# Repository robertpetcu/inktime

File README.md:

# InkTime - TSC

## Robert Cristian Petcu

# InkTime Smartwatch

InkTime is a smartwatch prototype built around the **nRF52840** SoC. The device features an **E-Paper display**, **BLE connectivity**, **battery charging and monitoring**, **motion sensing**, and **haptic feedback**, all integrated into a compact low-power wearable platform. The system is designed around a Li-Po battery, USB-C charging, an efficient 3.3V power stage, and a modular peripheral architecture.

---

## 1. Block Diagram

```text
+----------------------+
|      USB-C Port      |
+----------+-----------+
           |
           v
+----------------------+
|  Power / Charging IC |
|     BQ25180YBGR      |
+----------+-----------+
           |
           v
+----------------------+          +----------------------+
|    Li-Po Battery     |--------->|    3V3 Regulator    |
+----------------------+   VBAT   |      RT6160AWSC     |
                                  +----------+-----------+
                                             |
                                             v
                                   +----------------------+
                                   |     nRF52840 MCU     |
                                   |      MCU + BLE       |
                                   +---+----+----+---+----+
                                       |    |    |   |
                 USB ------------------+    |    |   +---------------- GPIO
                                       |    |    |                       |
                                       |    |    |                       +--> Buttons
                                       |    |    |
                                       |    |    +---------------- SWD
                                       |    |                            |
                                       |    |                            +--> SWD Debug
                                       |    |
                                       |    +---------------- I2C
                                       |                                 |
                                       |                                 +--> IMU (BMA421)
                                       |                                 |
                                       |                                 +--> Fuel Gauge (MAX17048G+T10)
                                       |                                 |
                                       |                                 +--> Haptic Driver (DRV2605YZFR)
                                       |                                                       |
                                       |                                                       +--> Haptic Motor
                                       |
                     SPI --------------+------------------------> E-Paper Display
                                       |                         (Display + E-Paper Drive)
                                       |
                     RF ---------------+------------------------> 2.4 GHz Antenna
                                                                 2450AT18B100E
                                                                
```

---

## 2. Bill of Materials (BOM)

### 2.1 Main Components

| Component | Designator(s) | Qty | Package | Purpose | JLC Parts | Datasheet |
|---|---|---:|---|---|---|---|
| nRF52840 | U1 | 1 | aQFN | Main MCU + BLE | [JLC Search](https://jlcpcb.com/parts/componentSearch?searchTxt=nRF52840) | [Nordic Product Page](https://www.nordicsemi.com/Products/nRF52840) |
| BQ25180YBGR | IC1 | 1 | BGA | Li-Po charging / power path | [JLC Search](https://jlcpcb.com/parts/componentSearch?searchTxt=BQ25180YBGR) | [TI Product Page](https://www.ti.com/product/BQ25180) |
| RT6160AWSC | IC9 | 1 | BGA | 3V3 regulator / DC-DC | [JLC Search](https://jlcpcb.com/parts/componentSearch?searchTxt=RT6160AWSC) | [Richtek Product Page](https://www.richtek.com/m/Products/Switching%20Regulators/Buck-Boost%20Converter/RT6160A?sc_lang=en) |
| BMA421 | IC3 | 1 | LGA | IMU sensor | [JLC Search](https://jlcpcb.com/parts/componentSearch?searchTxt=BMA421) | [Datasheet PDF](https://files.pine64.org/doc/datasheet/pinetime/BST-BMA421-FL000.pdf) |
| MAX17048G+T10 | U3 | 1 | SON / DFN | Fuel gauge | [JLC Search](https://jlcpcb.com/parts/componentSearch?searchTxt=MAX17048G%2BT10) | [Analog Devices Product Page](https://www.analog.com/en/products/max17048.html) |
| DRV2605YZFR | IC2 | 1 | DSBGA | Haptic driver | [JLC Search](https://jlcpcb.com/parts/componentSearch?searchTxt=DRV2605YZFR) | [TI Product Page](https://www.ti.com/product/DRV2605) |
| KH-TYPE-C-16P | J4 | 1 | SMD | USB-C connector | [JLC Search](https://jlcpcb.com/parts/componentSearch?searchTxt=KH-TYPE-C-16P) | [Datasheet PDF](https://datasheet.lcsc.com/lcsc/2404191039_Shenzhen-Kinghelm-Elec-KH-TYPE-C-16P_C709357.pdf) |
| 503480-2400 | J1 | 1 | FPC | E-paper display connector | [JLC Search](https://jlcpcb.com/parts/componentSearch?searchTxt=503480-2400) | [Molex Product Page](https://www.molex.com/en-us/products/part-detail/5034802400) |
| TC2030-IDC | J2 | 1 | Debug connector | SWD programming / debug | [JLC Search](https://jlcpcb.com/parts/componentSearch?searchTxt=TC2030-IDC) | [Tag-Connect Product Page](https://www.tag-connect.com/product/tc2030-idc-6-pin-tag-connect-plug-of-nails-spring-pin-cable-with-legs) |
| 2450AT18B100E | ANT1 | 1 | SMD antenna | 2.4 GHz antenna | [JLC Search](https://jlcpcb.com/parts/componentSearch?searchTxt=2450AT18B100E) | [Johanson Datasheet PDF](https://www.johansontechnology.com/docs/1187/2450AT18B100_X8XXogU.pdf) |
| 32 MHz crystal | X1 | 1 | 2016 | Main high-speed clock | [JLC Search](https://jlcpcb.com/parts/componentSearch?searchTxt=32MHz%202016) | [Search / vendor selection](https://jlcpcb.com/parts/componentSearch?searchTxt=32MHz%202016%20crystal) |
| 32.768 kHz crystal | X2 | 1 | 3215 | Low-power RTC clock | [JLC Search](https://jlcpcb.com/parts/componentSearch?searchTxt=32.768kHz%203215) | [Search / vendor selection](https://jlcpcb.com/parts/componentSearch?searchTxt=32.768kHz%203215%20crystal) |
| Buttons | SW_UP, SW_ENT, SW_DN | 3 | SMD | User input | [JLC Search](https://jlcpcb.com/parts/componentSearch?searchTxt=EVP-AKE31A) | [Panasonic Search](https://industry.panasonic.com/global/en/search?keyword=EVP-AKE31A) |
| USB ESD protection | D3 | 1 | SOT-23-6 | USB line protection | [JLC Search](https://jlcpcb.com/parts/componentSearch?searchTxt=USBLC6-2SC6Y) | [ST Product Page](https://www.st.com/en/protections-and-emi-filters/usblc6-2sc6y.html) |
| Schottky diodes | D2, D4, D5 | 3 | SMD | E-paper drive circuit | [JLC Search](https://jlcpcb.com/parts/componentSearch?searchTxt=MBR0530) | [onsemi Datasheet PDF](https://www.onsemi.com/download/data-sheet/pdf/mbr0530t1-d.pdf) |

---

## 3. Hardware Functionality Description

The InkTime smartwatch is built around the **nRF52840**, which acts as the main MCU and BLE controller. It manages the display, sensors, battery monitoring, haptic feedback, buttons, debugging, and RF communication.

### 3.1 Main MCU - nRF52840
The **nRF52840** is the central controller of the system. It was chosen for its:
- low power consumption
- BLE support
- SPI, I2C, USB, and SWD interfaces
- enough GPIOs for all peripherals

### 3.2 Power and Charging
The device is powered by a **Li-Po battery** and charged through **USB-C**. Charging and power-path management are handled by the **BQ25180YBGR**, while the **RT6160AWSC** generates the regulated **3.3V** supply for the system.

### 3.3 E-Paper Display
The display is connected through an **FPC connector** and controlled by the MCU over **SPI**. The display subsystem includes both the connector and the dedicated **e-paper drive circuit**.

### 3.4 IMU
Motion sensing is provided by the **BMA421**, connected over **I2C**. It is used for motion detection, gesture handling, and wake-up events.

### 3.5 Fuel Gauge
Battery monitoring is handled by the **MAX17048G+T10**, connected over **I2C**. It provides battery voltage and state-of-charge information to the MCU.

### 3.6 Haptic Driver
Haptic feedback is implemented using the **DRV2605YZFR**, also connected through **I2C**. It drives the vibration motor for notifications and user feedback.

### 3.7 Buttons
The device includes three buttons:
- **SW_UP**
- **SW_ENT**
- **SW_DN**

These are connected to GPIO pins and are used for user input and menu navigation.

### 3.8 SWD Debug
Programming and debugging are done through the **TC2030-IDC** SWD interface, which provides access to flashing and debugging during development.

### 3.9 RF Section
Wireless communication is handled by the nRF52840 through the **2450AT18B100E** 2.4 GHz antenna and its RF matching network.

---

## 4. nRF52840 Pin Usage

| Function | nRF52840 Pin | Description |
|---|---|---|
| EPD_CS | P0.05 | E-paper chip select |
| SDA | P0.06 | I2C data line |
| SCL | P0.07 | I2C clock line |
| IMU_INT1 | P0.08 | IMU interrupt 1 |
| IMU_INT2 | P1.08 | IMU interrupt 2 |
| Fuel Gauge ALERT | P0.10 | Battery alert signal |
| PMIC_INT | P0.11 | Charger / PMIC interrupt |
| HAPTIC_EN | P0.12 | Haptic control / enable |
| SW_UP | P0.13 | Button input |
| SW_ENT | P0.14 | Button input |
| SW_DN | P1.02 | Button input |
| SWDIO | SWDIO | Debug data |
| SWDCLK | SWDCLK | Debug clock |
| RESET | P0.18 / RESET | System reset |
| USB D+ / D- | Dedicated USB pins | USB interface |
| RF ANT | ANT | Antenna connection |

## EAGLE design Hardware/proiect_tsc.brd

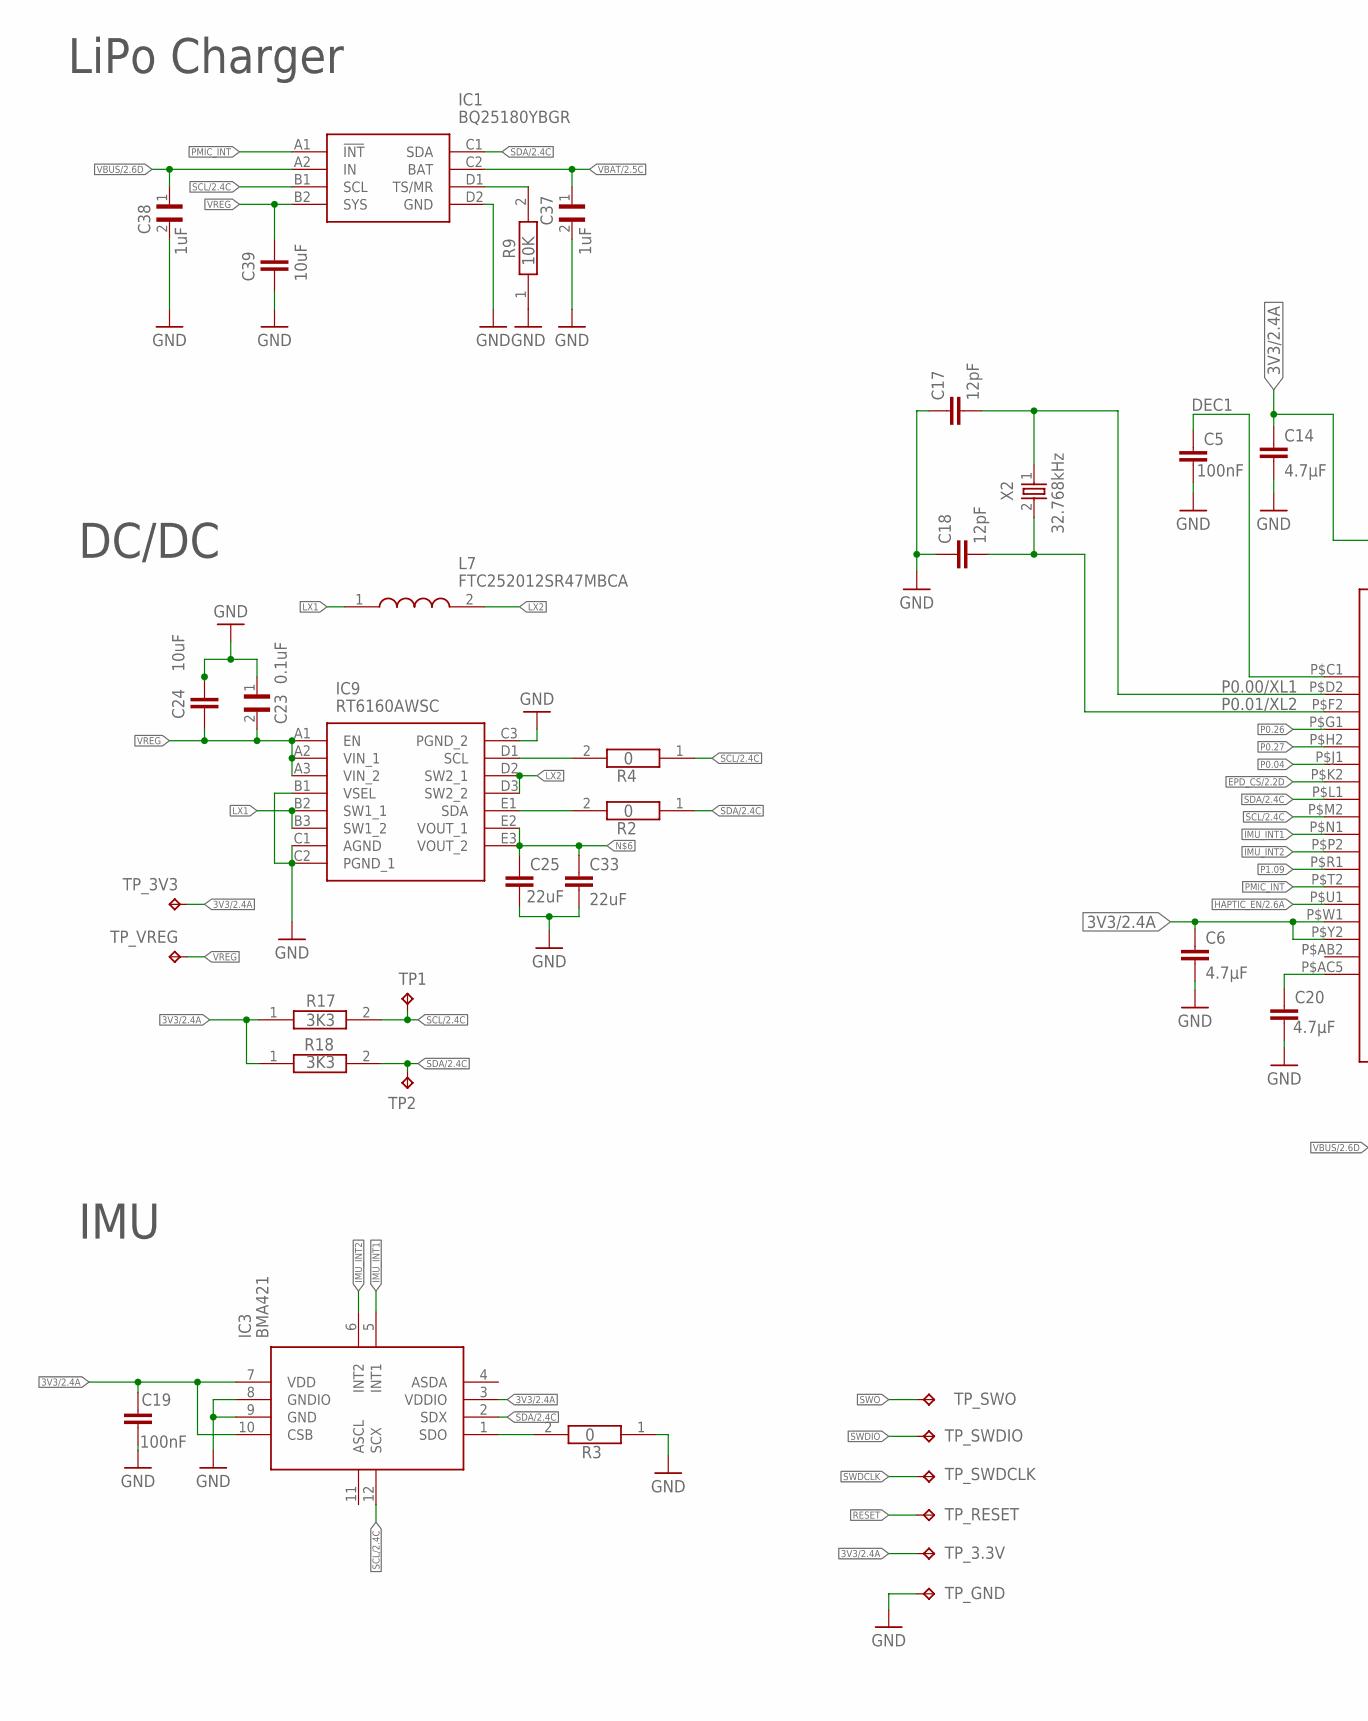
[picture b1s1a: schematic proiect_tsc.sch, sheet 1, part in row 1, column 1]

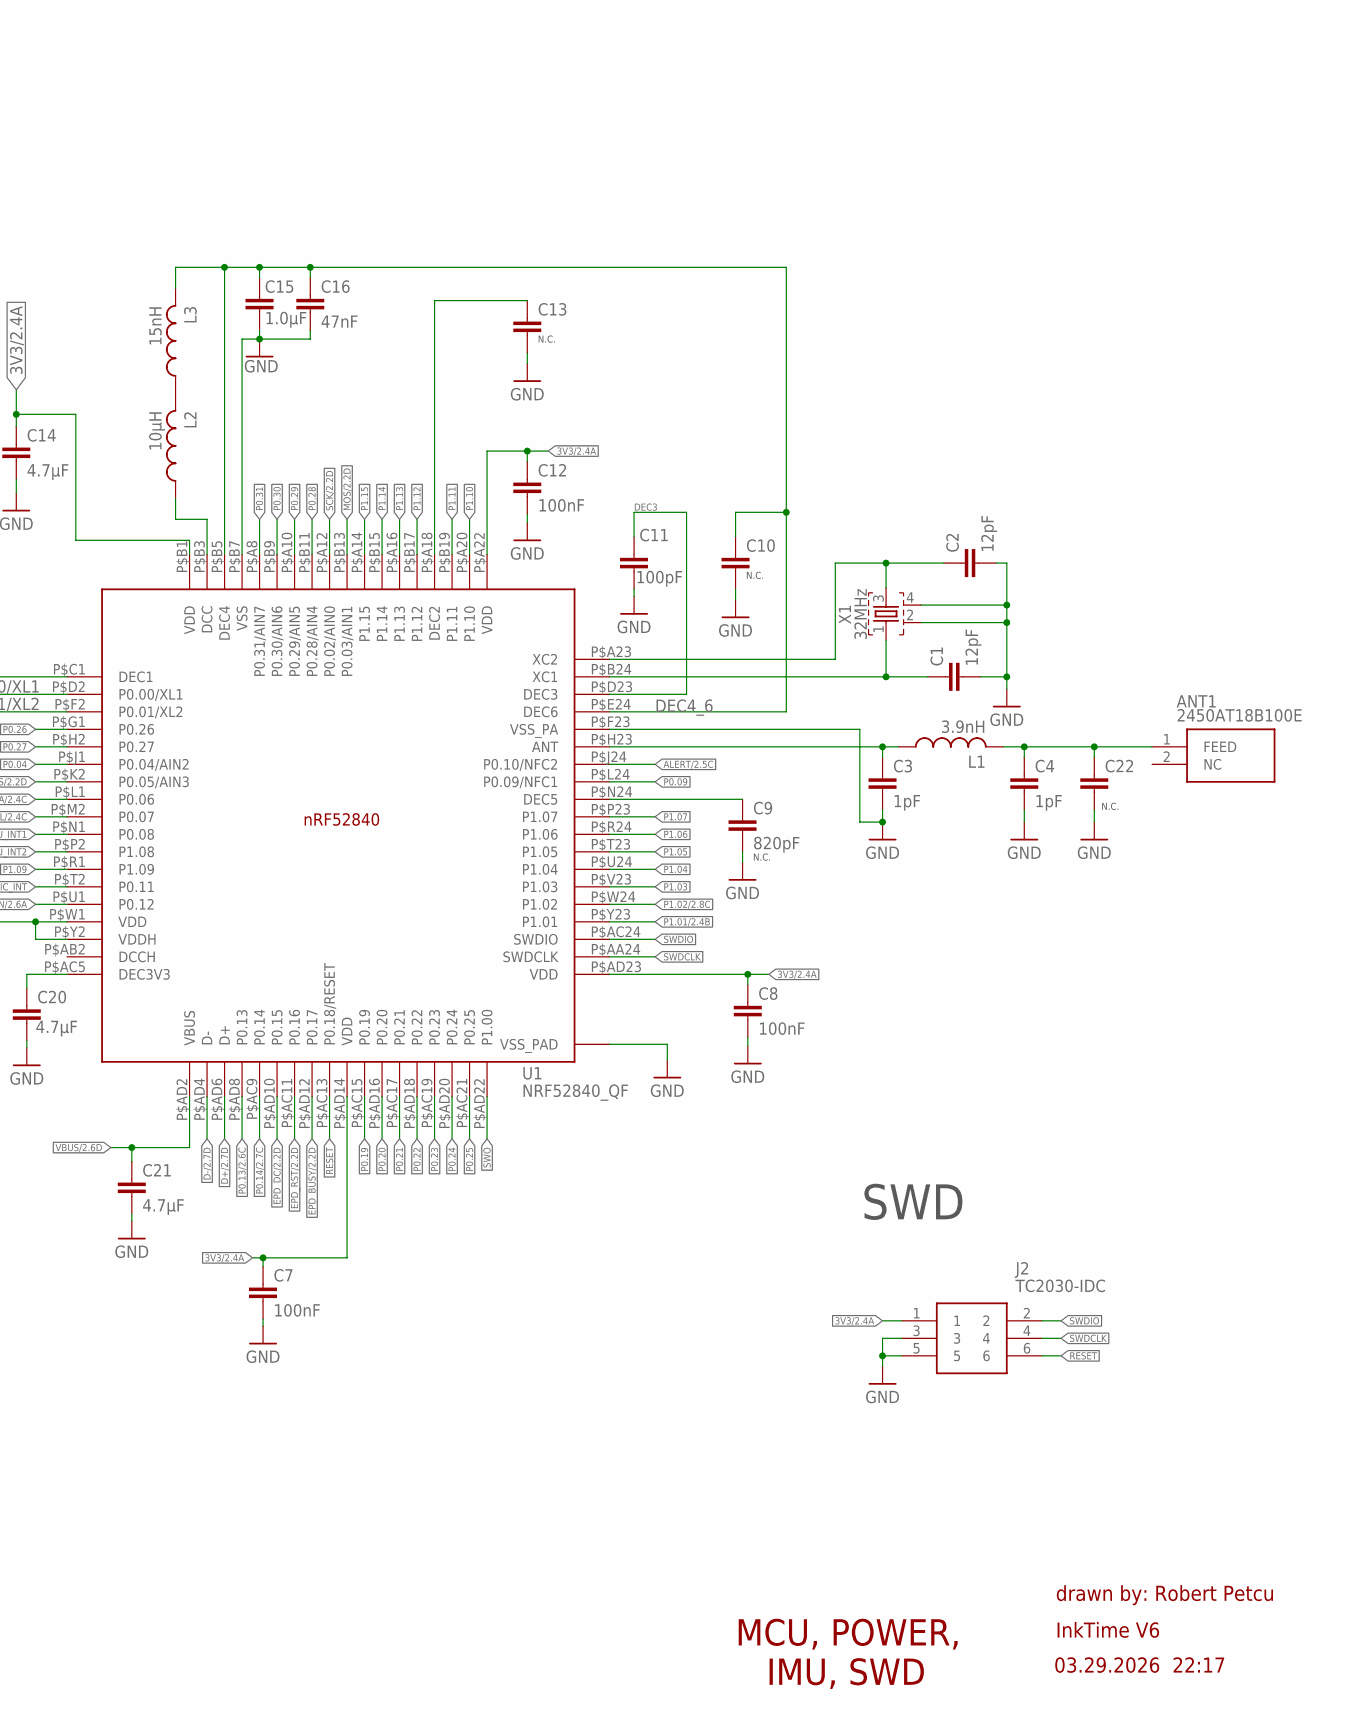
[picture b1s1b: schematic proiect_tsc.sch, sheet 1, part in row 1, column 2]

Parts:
ANT1: 2450AT18B100E; 2450AT18B100E_ANTC3216X140N
C1, C2, C17, C18: 12pF; NORDIC_NRF_3_RESC0201_L
C3, C4: 1pF; NORDIC_NRF_3_RESC0201_L
C5, C7, C8, C12, C19: 100nF; NORDIC_NRF_3_RESC0201_L
C6, C14, C20, C21: 4.7µF; PERFECT_0402_0402
C9: 820pF; NORDIC_NRF_3_RESC0201_L
C10, C13, C22: NORDIC_NRF_3_CAPACITOR_0201_L; NORDIC_NRF_3_RESC0201_L
C11: 100pF; NORDIC_NRF_3_RESC0201_L
C15: 1.0µF; PERFECT_0402_0402
C16: 47nF; NORDIC_NRF_3_RESC0201_L
C23: 0.1uF; GRM011R60J152KE01L_1_0201
C24, C39: 10uF; PERFECT_0402_0402
C25, C33: 22uF; PERFECT_0402_0402
C37, C38: 1uF; GRM011R60J152KE01L_1_0201
IC1: BQ25180YBGR; BQ25180YBGR_BGA8C40P2X4_100X155X50
IC3: BMA421; BMA423_BMA423
IC9: RT6160AWSC; RT6160AWSC_BGA15C40P3X5_140X230X60
J2: TC2030-IDC; TC2030-IDC_TC2030IDC
L1: 3.9nH; NORDIC_NRF_2_RESC0402_L
L2: 10µH; NORDIC_NRF_2_RESC0402_L
L3: 15nH; NORDIC_NRF_2_RESC0402_L
L7: FTC252012SR47MBCA; MLP2016SR47MT0S1_INDC2016X100N
R2, R3, R4: 0; CPF0201D7K68C1_0201
R9: 10K; CPF0201D7K68C1_0201
R17, R18: 3K3; CPF0201D7K68C1_0201
TP1, TP2: HECTOR_WATCH_1_TPTP20R; HECTOR_WATCH_1_TP20R
TP_3.3V, TP_3V3: HECTOR_WATCH_1_TPTP20R; HECTOR_WATCH_1_TP20R
TP_GND: HECTOR_WATCH_1_TPTP20R; HECTOR_WATCH_1_TP20R
TP_RESET: HECTOR_WATCH_1_TPTP20R; HECTOR_WATCH_1_TP20R
TP_SWDCLK: HECTOR_WATCH_1_TPTP20R; HECTOR_WATCH_1_TP20R
TP_SWDIO: HECTOR_WATCH_1_TPTP20R; HECTOR_WATCH_1_TP20R
TP_SWO: HECTOR_WATCH_1_TPTP20R; HECTOR_WATCH_1_TP20R
TP_VREG: HECTOR_WATCH_1_TPTP20R; HECTOR_WATCH_1_TP20R
U1: NRF52840_QF; NORDIC_NRF_4_AQFN50P700X700X85_HS-74N
X1: 32MHz; NORDIC_NRF_BT-XTAL_2016_N
X2: 32.768kHz; NORDIC_NRF_1_XTAL_3215_N

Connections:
3V3/2.4A: C6.1, C7.1, C8.1, C12.1, C14.1, C19.1, IC3.3 (VDDIO), IC3.7 (VDD), IC3.10 (CSB), J2.1, R17.1, R18.1, TP_3.3V.TP, TP_3V3.TP, U1.P$A22 (VDD), U1.P$AD14 (VDD), U1.P$AD23 (VDD), U1.P$B1 (VDD), U1.P$W1 (VDD), U1.P$Y2 (VDDH)
ALERT/2.5C: U1.P$J24 (P0.10/NFC2)
D+/2.7D: U1.P$AD6 (D+)
D-/2.7D: U1.P$AD4 (D-)
DEC1: C5.1, U1.P$C1 (DEC1)
DEC3: C11.1, U1.P$D23 (DEC3)
DEC4_6: C10.1, C15.1, C16.1, L3.2, U1.P$B5 (DEC4), U1.P$E24 (DEC6)
EPD_BUSY/2.2D: U1.P$AD12 (P0.17)
EPD_CS/2.2D: U1.P$K2 (P0.05/AIN3)
EPD_DC/2.2D: U1.P$AD10 (P0.15)
EPD_RST/2.2D: U1.P$AC11 (P0.16)
GND: C1.2, C2.2, C3.2, C4.2, C5.2, C6.2, C7.2, C8.2, C9.2, C10.2, C11.2, C12.2, C13.2, C14.2, C15.2, C16.2, C17.1, C18.1, C19.2, C20.2, C21.2, C22.2, C23.1, C24.1, C25.2, C33.2, C37.2, C38.2, C39.2, IC1.D2 (GND), IC3.8 (GNDIO), IC3.9 (GND), IC9.B1 (VSEL), IC9.C1 (AGND), IC9.C2 (PGND_1), IC9.C3 (PGND_2), J2.3, J2.5, R3.1, R9.1, TP_GND.TP, U1.P$74 (VSS_PAD), U1.P$75 (VSS_PAD), U1.P$76 (VSS_PAD), U1.P$77 (VSS_PAD), U1.P$78 (VSS_PAD), U1.P$79 (VSS_PAD), U1.P$80 (VSS_PAD), U1.P$81 (VSS_PAD), U1.P$82 (VSS_PAD), U1.P$83 (VSS_PAD), U1.P$84 (VSS_PAD), U1.P$85 (VSS_PAD), U1.P$86 (VSS_PAD), U1.P$87 (VSS_PAD), U1.P$88 (VSS_PAD), U1.P$89 (VSS_PAD), U1.P$90 (VSS_PAD), U1.P$B7 (VSS), U1.P$F23 (VSS_PA), X1.2, X1.4; also elsewhere on the board
HAPTIC_EN/2.6A: U1.P$U1 (P0.12)
IMU_INT1: IC3.5 (INT1), U1.P$N1 (P0.08)
IMU_INT2: IC3.6 (INT2), U1.P$P2 (P1.08)
LX1: IC9.B2 (SW1_1), IC9.B3 (SW1_2), L7.1
LX2: IC9.D2 (SW2_1), IC9.D3 (SW2_2), L7.2
MOS/2.2D: U1.P$B13 (P0.03/AIN1)
unnamed: IC9.D1 (SCL), R4.2
unnamed: IC9.E1 (SDA), R2.2
unnamed: IC1.D1 (TS/MR), R9.2
unnamed: C25.1, C33.1, IC9.E2 (VOUT_1), IC9.E3 (VOUT_2)
unnamed: L2.1, U1.P$B3 (DCC)
unnamed: C20.1, U1.P$AC5 (DEC3V3)
unnamed: IC3.1 (SDO), R3.2
unnamed: L2.2, L3.1
unnamed: C2.1, U1.P$A23 (XC2), X1.3
unnamed: C13.1, U1.P$A18 (DEC2)
unnamed: C9.1, U1.P$N24 (DEC5)
unnamed: C1.1, U1.P$B24 (XC1), X1.1
unnamed: C3.1, L1.1, U1.P$H23 (ANT)
unnamed: ANT1.1 (FEED), C4.1, C22.1, L1.2
P0.00/XL1: C17.2, U1.P$D2 (P0.00/XL1), X2.1
P0.01/XL2: C18.2, U1.P$F2 (P0.01/XL2), X2.2
P0.04: U1.P$J1 (P0.04/AIN2)
P0.09: U1.P$L24 (P0.09/NFC1)
P0.13/2.6C: U1.P$AD8 (P0.13)
P0.14/2.7C: U1.P$AC9 (P0.14)
P0.19: U1.P$AC15 (P0.19)
P0.20: U1.P$AD16 (P0.20)
P0.21: U1.P$AC17 (P0.21)
P0.22: U1.P$AD18 (P0.22)
P0.23: U1.P$AC19 (P0.23)
P0.24: U1.P$AD20 (P0.24)
P0.25: U1.P$AC21 (P0.25)
P0.26: U1.P$G1 (P0.26)
P0.27: U1.P$H2 (P0.27)
P0.28: U1.P$B11 (P0.28/AIN4)
P0.29: U1.P$A10 (P0.29/AIN5)
P0.30: U1.P$B9 (P0.30/AIN6)
P0.31: U1.P$A8 (P0.31/AIN7)
P1.01/2.4B: U1.P$Y23 (P1.01)
P1.02/2.8C: U1.P$W24 (P1.02)
P1.03: U1.P$V23 (P1.03)
P1.04: U1.P$U24 (P1.04)
P1.05: U1.P$T23 (P1.05)
P1.06: U1.P$R24 (P1.06)
P1.07: U1.P$P23 (P1.07)
P1.09: U1.P$R1 (P1.09)
P1.10: U1.P$A20 (P1.10)
P1.11: U1.P$B19 (P1.11)
P1.12: U1.P$B17 (P1.12)
P1.13: U1.P$A16 (P1.13)
P1.14: U1.P$B15 (P1.14)
P1.15: U1.P$A14 (P1.15)
PMIC_INT: IC1.A1 (!INT), U1.P$T2 (P0.11)
RESET: J2.6, TP_RESET.TP, U1.P$AC13 (P0.18/RESET)
SCK/2.2D: U1.P$A12 (P0.02/AIN0)
SCL/2.4C: IC1.B1 (SCL), IC3.12 (SCX), R4.1, R17.2, TP1.TP, U1.P$M2 (P0.07)
SDA/2.4C: IC1.C1 (SDA), IC3.2 (SDX), R2.1, R18.2, TP2.TP, U1.P$L1 (P0.06)
SWDCLK: J2.4, TP_SWDCLK.TP, U1.P$AA24 (SWDCLK)
SWDIO: J2.2, TP_SWDIO.TP, U1.P$AC24 (SWDIO)
SWO: TP_SWO.TP, U1.P$AD22 (P1.00)
VBAT/2.5C: C37.1, IC1.C2 (BAT)
VBUS/2.6D: C21.1, C38.1, IC1.A2 (IN), U1.P$AD2 (VBUS)
VREG: C23.2, C24.2, C39.1, IC1.B2 (SYS), IC9.A1 (EN), IC9.A2 (VIN_1), IC9.A3 (VIN_2), TP_VREG.TP

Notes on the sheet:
N.C.
N.C.
LiPo Charger
DC/DC
IMU
SWD
MCU, POWER, IMU, SWD
drawn by: Robert Petcu
InkTime V6
03.29.2026 22:17

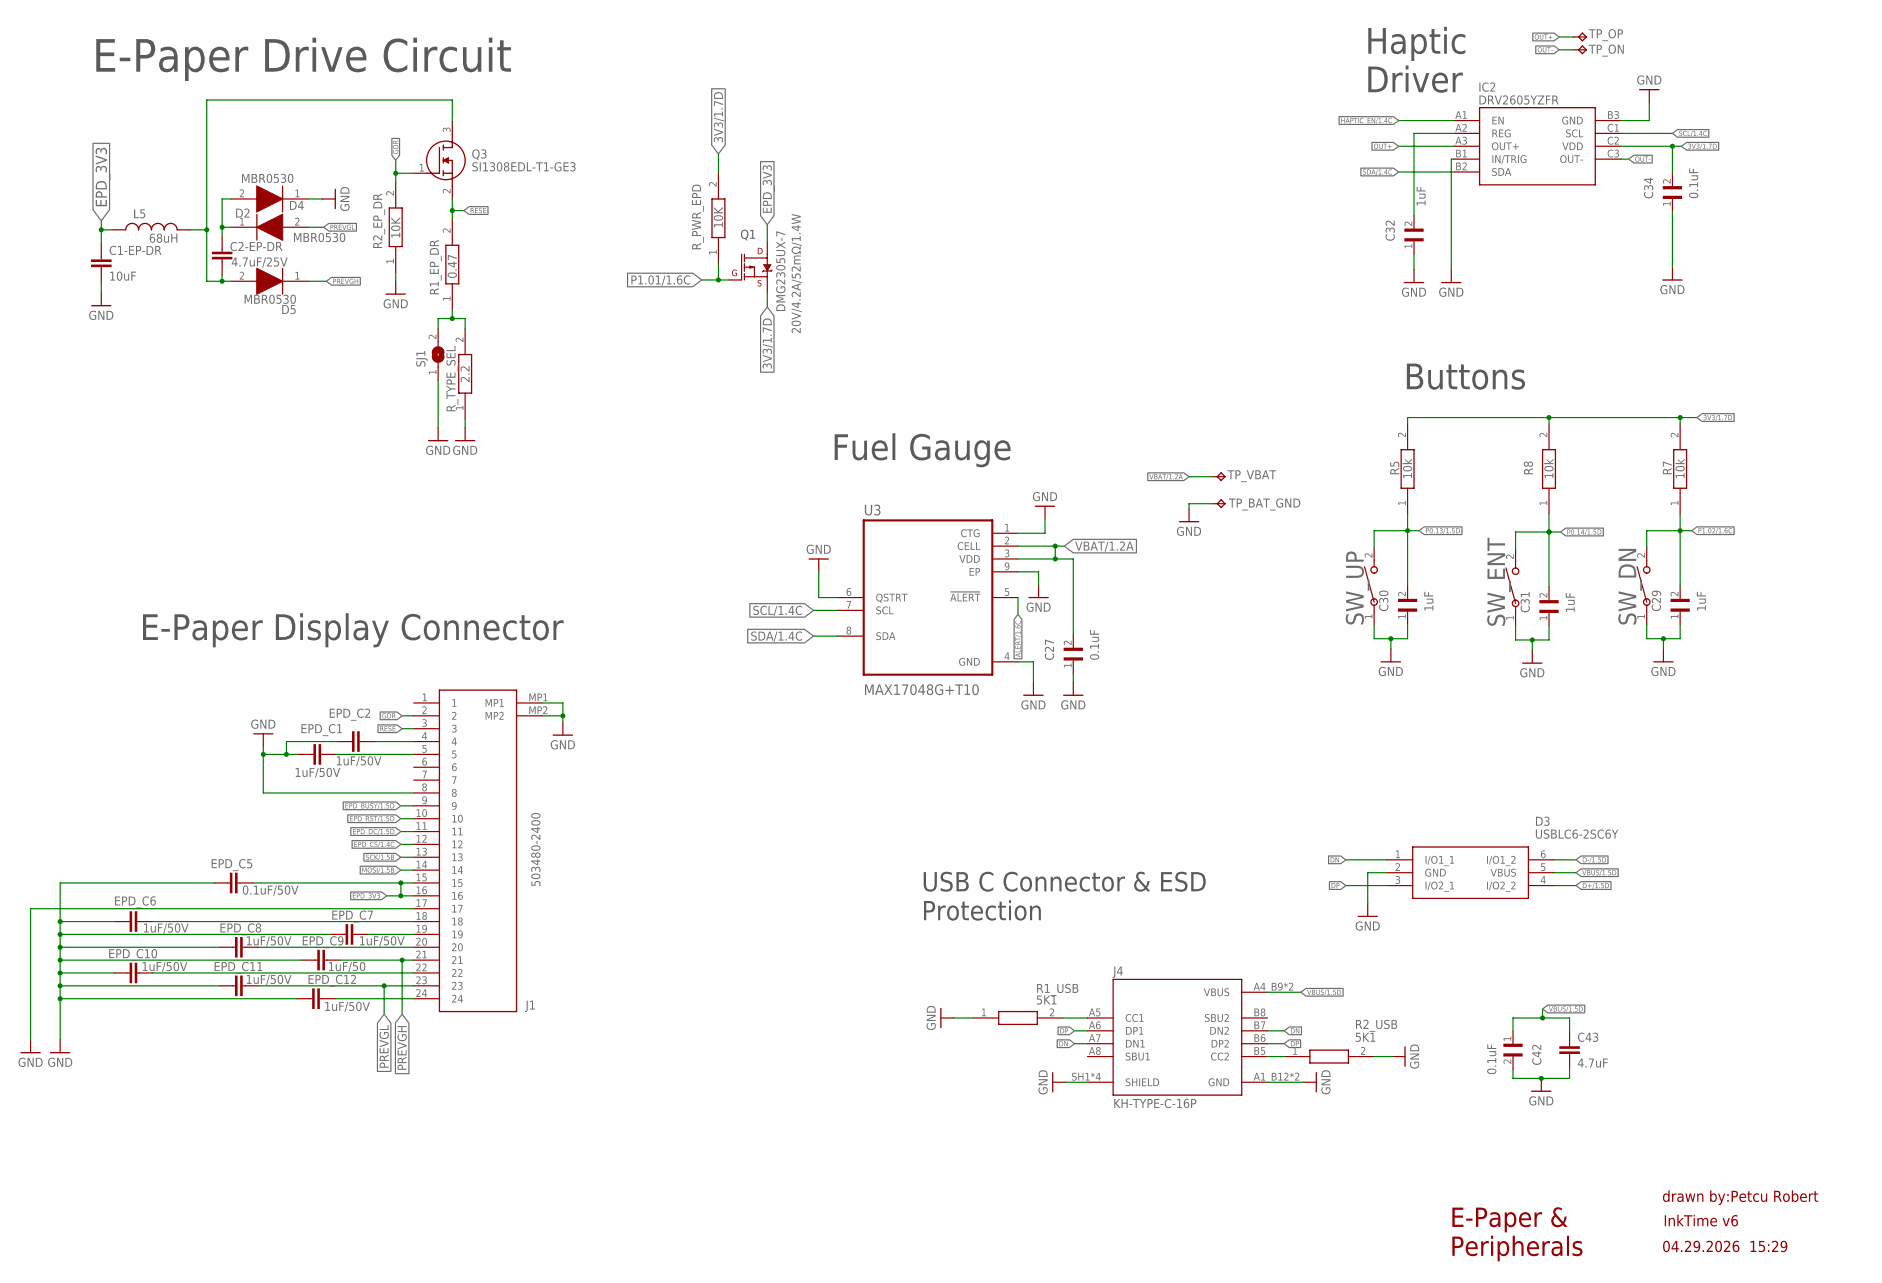
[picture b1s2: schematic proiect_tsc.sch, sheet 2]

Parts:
C1-EP-DR: 10uF; PERFECT_0402_0402
C2-EP-DR: 4.7uF/25V; PERFECT_0402_0402
C27, C34, C42: 0.1uF; GRM011R60J152KE01L_1_0201
C29, C30, C31, C32: 1uF; GRM011R60J152KE01L_1_0201
C43: 4.7uF; PERFECT_0402_0402
D2, D4, D5: MBR0530; ESP32_C6_LIBRARY_5_SOD3716X135N
D3: USBLC6-2SC6Y; ESP32_C6_LIBRARY_3_SOT95P280X145-6N
DMG2305UX-7: 20V/4.2A/52mΩ/1.4W; ESP32_C6_LIBRARY_4_ESP32_C6_LIBRARY_4_ESP32_C6_LIBRARY_4_ES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
EPD_C1, EPD_C2, EPD_C6, EPD_C7, EPD_C8, EPD_C10, EPD_C11, EPD_C12: 1uF/50V; PERFECT_0402_0402
EPD_C5: 0.1uF/50V; NORDIC_NRF_3_RESC0201_L
EPD_C9: 1uF/50; PERFECT_0402_0402
IC2: DRV2605YZFR; DRV2605YZFR_BGA9C50P3X3_144X144X62
J1: 503480-2400; 503480-2400_5034802400
J4: KH-TYPE-C-16P; KH-TYPE-C-16P_KINGHELM_KH-TYPE-C-16P
L5: 68uH; NORDIC_NRF_2_RESC0402_L
Q3: SI1308EDL-T1-GE3; ESP32_C6_LIBRARY_6_SOT65P210X110-3N
R1_EP_DR: 0.47; CPF0201D7K68C1_0201
R1_USB, R2_USB: 5K1; CPF0201D7K68C1_0201
R2_EP_DR: 10K; CPF0201D7K68C1_0201
R5, R7, R8: 10k; CPF0201D7K68C1_0201
R_PWR_EPD: 10K; CPF0201D7K68C1_0201
R_TYPE_SEL: 2.2; CPF0201D7K68C1_0201
SJ1: ESP32_C6_LIBRARY_7_JUMPER_SJ
SW_DN: 2025-10-22_07-23-44_LIBRARY_EVP-AKE31ASW_EVP-AKE3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; 2025-10-22_07-23-44_LIBRARY_SW_EVP-AKE31A_PAN
SW_ENT: 2025-10-22_07-23-44_LIBRARY_EVP-AKE31ASW_EVP-AKE3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; 2025-10-22_07-23-44_LIBRARY_SW_EVP-AKE31A_PAN
SW_UP: 2025-10-22_07-23-44_LIBRARY_EVP-AKE31ASW_EVP-AKE3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; 2025-10-22_07-23-44_LIBRARY_SW_EVP-AKE31A_PAN
TP_BAT_GND: HECTOR_WATCH_1_TPTP20R; HECTOR_WATCH_1_TP20R
TP_ON: HECTOR_WATCH_1_TPTP20R; HECTOR_WATCH_1_TP20R
TP_OP: HECTOR_WATCH_1_TPTP20R; HECTOR_WATCH_1_TP20R
TP_VBAT: HECTOR_WATCH_1_TPTP20R; HECTOR_WATCH_1_TP20R
U3: MAX17048G+T10; ESP32_C6_LIBRARY_SON50P200X200X80-9N

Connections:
3V3/1.7D: C34.2, DMG2305UX-7.2 (S), IC2.C2 (VDD), R5.2, R7.2, R8.2, R_PWR_EPD.2
ALERT/1.6C: U3.5 (!ALERT)
D+/1.5D: D3.4 (I/O2_2)
D-/1.5D: D3.6 (I/O1_2)
DN: D3.1 (I/O1_1), J4.A7 (DN1), J4.B7 (DN2)
DP: D3.3 (I/O2_1), J4.A6 (DP1), J4.B6 (DP2)
EPD_3V3: C1-EP-DR.1, DMG2305UX-7.3 (D), EPD_C5.2, J1.15, J1.16, L5.1
EPD_BUSY/1.5D: J1.9
EPD_CS/1.4C: J1.12
EPD_DC/1.5D: J1.11
EPD_RST/1.5D: J1.10
GDR: J1.2, Q3.1 (G), R2_EP_DR.2
GND: C1-EP-DR.2, C27.1, C29.1, C30.1, C31.1, C32.1, C34.1, C42.2, C43.2, D3.2 (GND), D4.1 (K), EPD_C1.1, EPD_C2.1, EPD_C5.1, EPD_C6.1, EPD_C7.1, EPD_C8.1, EPD_C9.1, EPD_C10.1, EPD_C11.1, EPD_C12.1, IC2.B1 (IN/TRIG), IC2.B3 (GND), J1.8, J1.17, J1.MP1, J1.MP2, J4.A1_B12 (GND), J4.A12_B1 (GND), J4.SH1 (SHIELD), J4.SH2 (SHIELD), J4.SH3 (SHIELD), J4.SH4 (SHIELD), R1_USB.1, R2_EP_DR.1, R2_USB.2, R_TYPE_SEL.1, SJ1.1, SW_DN.1, SW_ENT.1, SW_UP.1, TP_BAT_GND.TP, U3.1 (CTG), U3.4 (GND), U3.6 (QSTRT), U3.9 (EP); also elsewhere on the board
HAPTIC_EN/1.4C: IC2.A1 (EN)
MOSI/1.5B: J1.14
unnamed: C2-EP-DR.2, D5.2 (A), L5.2, Q3.3 (D)
unnamed: C2-EP-DR.1, D2.1 (K), D4.2 (A)
unnamed: EPD_C6.2, J1.18
unnamed: R1_EP_DR.1, R_TYPE_SEL.2, SJ1.2
unnamed: EPD_C2.2, J1.4
unnamed: EPD_C1.2, J1.5
unnamed: EPD_C7.2, J1.19
unnamed: EPD_C8.2, J1.20
unnamed: C32.2, IC2.A2 (REG)
unnamed: EPD_C10.2, J1.22
unnamed: J4.A5 (CC1), R1_USB.2
unnamed: EPD_C12.2, J1.24
unnamed: J4.B5 (CC2), R2_USB.1
OUT+: IC2.A3 (OUT+), TP_OP.TP
OUT-: IC2.C3 (OUT-), TP_ON.TP
P0.13/1.5D: C30.2, R5.1, SW_UP.2
P0.14/1.5D: C31.2, R8.1, SW_ENT.2
P1.01/1.6C: DMG2305UX-7.1 (G), R_PWR_EPD.1
P1.02/1.6C: C29.2, R7.1, SW_DN.2
PREVGH: D5.1 (K), EPD_C9.2, J1.21
PREVGL: D2.2 (A), EPD_C11.2, J1.23
RESE: J1.3, Q3.2 (S), R1_EP_DR.2
SCK/1.5B: J1.13
SCL/1.4C: IC2.C1 (SCL), U3.7 (SCL)
SDA/1.4C: IC2.B2 (SDA), U3.8 (SDA)
VBAT/1.2A: C27.2, TP_VBAT.TP, U3.2 (CELL), U3.3 (VDD)
VBUS/1.5D: C42.1, C43.1, D3.5 (VBUS), J4.A4_B9 (VBUS), J4.A9_B4 (VBUS)

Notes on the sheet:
E-Paper Drive Circuit
E-Paper Display Connector
Fuel Gauge
Buttons
Haptic Driver
USB C Connector & ESD Protection
E-Paper & Peripherals
drawn by:Petcu Robert
InkTime v6
04.29.2026 15:29

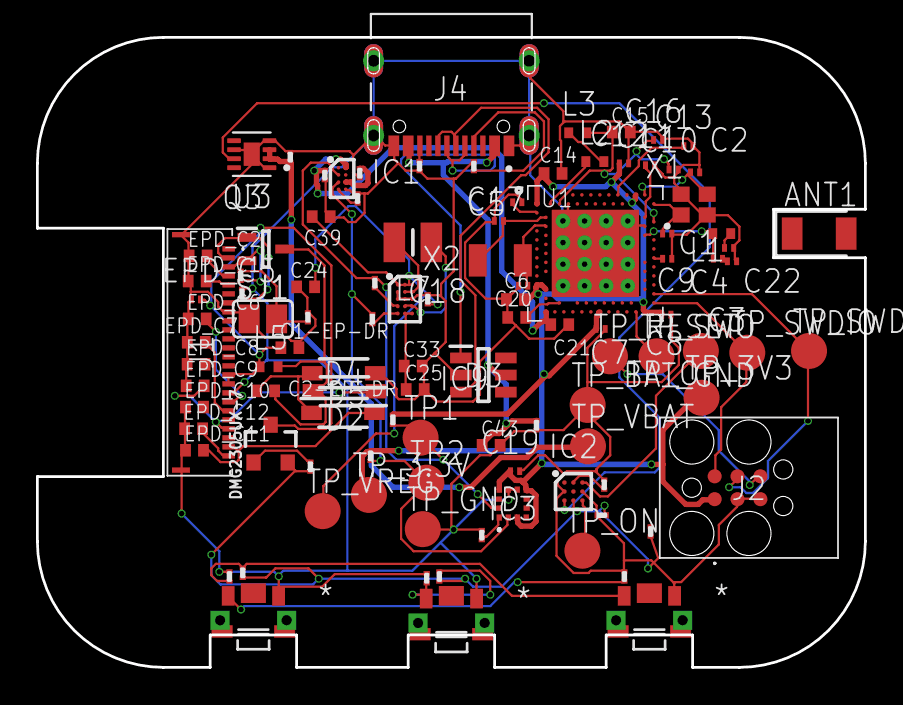
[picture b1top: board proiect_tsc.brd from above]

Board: 2 copper layers, 46.0 x 35.0 mm, 105 parts (0 on the bottom side), 66 nets.

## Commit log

2026-04-10 Init
2026-04-22 After review updates
2026-04-22 more images

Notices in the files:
parts and their libraries:
COPYRIGHT: Copyright (C) 2025 Ultra Librarian. All rights reserved.
